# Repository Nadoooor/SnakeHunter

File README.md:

# SnakeHunter
A Handheld device that clones differenet signals like IR, RFID, and more. It has a battery to make it handheld and work without powersource like the laptop.<br>
I made this project because I love cybersecurity specialy networks and the idea of cloneing them. Also, I love hardware so much so combineing the both in one project is sooo cool. 

### Modules used:
- RFID Read/Write
- NRF24L01 Wireless Module With Antenna
- Ublox NEO-6m GPS Module
- Infrared Remote Receiver TSOP JS-1838B
- Infrared LED Diode (Transmitter)
- XL6009 DC-DC Step UP Boost Converter Module (3A) 
### Photos

 <br>

### BOM (Bill Of Materials)
| Item                                                         | Link                                                                                                                                                                                                                                                                                                                                                                                                                                                                                                     | Price                  |
|--------------------------------------------------------------|----------------------------------------------------------------------------------------------------------------------------------------------------------------------------------------------------------------------------------------------------------------------------------------------------------------------------------------------------------------------------------------------------------------------------------------------------------------------------------------------------------|------------------------|
| ESP32 38pins                                                 | [Link](https://mostelectronic.com/shop/arduino-development-boards/esp32-s-38pin-development-board-wifi-and-bluetooth/)                                                                                                                                                                                                                                                                                                                                                                                           | $8.08                  |
| TFT LCD touch screen                                         | [Link](https://www.amazon.com/WWZMDiB-Display-Interface-Arduino-320x240/dp/B0CCHXX1Z9/ref=sr_1_1_sspa?dib=eyJ2IjoiMSJ9.9xYzrIvxxHsHdfW-gksWb3jXxskzgUuA5Zv92-vbF_rgpDSizUJq9ZgjkUXXAnXTFF-g7tu8c3U8-EMJlw-Q9uDaEn5B7V5boVKGWRNHZUFaeOUc-jy6nT_AmLIXFEHbz0vlXF-KDvlwjrPltPtbK0t41pq8tB6F4K7ICLWzThnjkHNXrFFSCCIgBb_lXGixU3_zdR4z01ZQVJP6Scx8_LsG3fd-tv3Qi1mEAhEKbvs.DzTPSmzNNeTbDCBnk1YsSWki1K8MFNSX6Lj1MkVzSLU&dib_tag=se&keywords=tft+display&qid=1752311294&sr=8-1-spons&sp_csd=d2lkZ2V0TmFtZT1zcF9hdGY&psc=1) | $35.07 (with shipping) |
| 3D printed case                                              |                                                                                                                                                                                                                                                                                                                                                                                                                                                                                                          | $10.10                 |
| RFID Read/Write                                              | [Link](https://mostelectronic.com/shop/sensors/rfid-read-write-module-mfrc-522-13-56-mhz/ )                                                                                                                                                                                                                                                                                                                                                                                                                      | $2.42                  |
| Battery X3                                                   | [Link](https://mostelectronic.com/shop/batteries-accessories/rechargeable-batteries/rechargeable-402030-lipo-battery-cell-3-7v-350mah-wire-solder/)                                                                                                                                                                                                                                                                                                                                                          | $3.94                  |
| PCB FR2 Circuit Board (7 x10) cm Pointing                    | [Link](https://mostelectronic.com/shop/pcb/pcb-pcb/pcb-fr2-circuit-board-7-x10-cm-pointing/)                                                                                                                                                                                                                                                                                                                                                                                                                     | $1                     |
| Solder Wire                                                  | [Link](https://mostelectronic.com/shop/tools/soldering-desoldering/solder-wire-singapore-250g-0-6mm-70-30-singapore/)                                                                                                                                                                                                                                                                                                                                                                                            | $11.11                 |
| NRF24L01 Wireless Module With Antenna                        | [Link](https://mostelectronic.com/shop/sensors/nrf24l01-wireless-module-with-antenna/)                                                                                                                                                                                                                                                                                                                                                                                                                           | $6.26                  |
| Cutter Knife                                                 | [Link](https://mostelectronic.com/shop/tools/wire-strippers-nipples-pliers/cutter-knife/)                                                                                                                                                                                                                                                                                                                                                                                                                       | $0.5                   |
| BMS 1S TP4056 (5V -1A) ( Type C ) With Protection            | [Link](https://mostelectronic.com/shop/batteries-accessories/battery-accessories/bms-1s-tp4056-5v-1a-lithium-battery-charger-board-type-c-with-protection/)                                                                                                                                                                                                                                                                                                                                                      | $0.5                   |
| Ublox NEO-6m GPS Module                                      | [Link](https://mostelectronic.com/shop/sensors/ublox-neo-6m-gps-module/)                                                                                                                                                                                                                                                                                                                                                                                                                                        | $9.09                  |
| Infrared Remote Receiver TSOP JS-1838B                       | [Link](https://mostelectronic.com/shop/sensors/infrared-receiver-diode-tl1838-vs1838b/)                                                                                                                                                                                                                                                                                                                                                                                                                         | $0.20                  |
| Infrared LED Diode (Transmitter)                             | [Link](https://mostelectronic.com/shop/sensors/infrared-led-diode-transmitter/)                                                                                                                                                                                                                                                                                                                                                                                                                                  | $0.051                 |
| Micro SD Card Modul                                          | [Link](https://mostelectronic.com/shop/sensors/micro-sd-card-module/)                                                                                                                                                                                                                                                                                                                                                                                                                                            | $1                     |
| XL6009 DC-DC Step UP Boost Converter Module (3A)             | [Link](https://mostelectronic.com/shop/dc-ac-converters/dc-dc-step-up-boost-converter-module-xl6009-3a/)                                                                                                                                                                                                                                                                                                                                                                                                         | $1.41                  |
| DIP Switch 2 Way                                             | [Link](https://mostelectronic.com/shop/components/switches/dip-switch-2-way/)                                                                                                                                                                                                                                                                                                                                                                                                                                    | $0.081                 |
| Connecting Jumper Wires for Breadboard ( 140 Wire – U shape) | [Link](https://mostelectronic.com/shop/wires-crocodiles/u-shape-shield-breadboard-jumper-wires-140pcs/)                                                                                                                                                                                                                                                                                                                                                                                                         | $1.11                  |
|SD card | [Link](https://www.noon.com/egypt-en/canvasselect-plus-micro-sdhc-memory-card-with-adapter-32-gb/N43383398A/p/?o=dd29d760fc2d52bb&shareId=a9b190a7-fcdf-448a-a7b9-24fdeadd19a3) | $5|
| Shipping                                                     |                                                                                                                                                                                                                                                                                                                                                                                                                                                                                                          | $3                     |
| Total                                                        |                                                                                                                                                                                                                                                                                                                                                                                                                                                                                                          | 95$                    |

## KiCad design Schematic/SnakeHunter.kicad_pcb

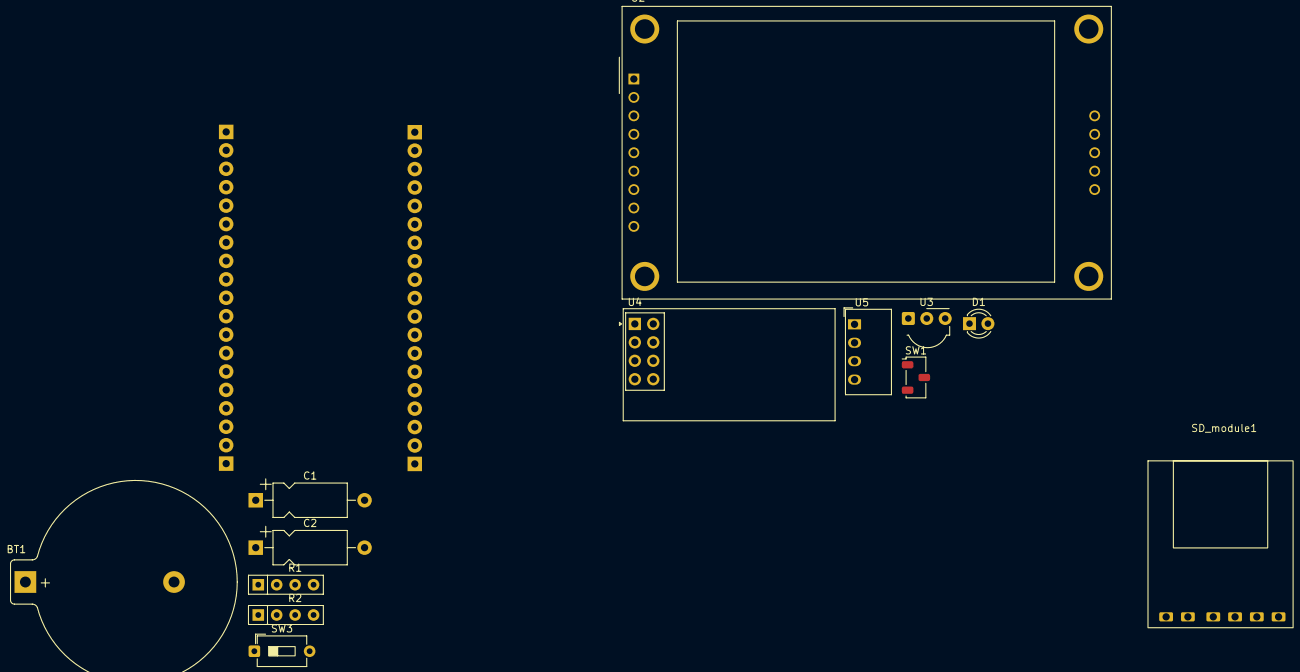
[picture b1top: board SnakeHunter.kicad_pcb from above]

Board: 2 copper layers, 14 parts (0 on the bottom side), 19 nets, no tracks yet.

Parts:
BT1: Battery; BatteryHolder_Keystone_106_1x20mm
C1: C; CP_Axial_L10.0mm_D4.5mm_P15.00mm_Horizontal
C2: C_Polarized; CP_Axial_L10.0mm_D4.5mm_P15.00mm_Horizontal
D1: IR204A; LED_D3.0mm_IRBlack
R1, R2: R; R_Array_SIP4
SD_module1: SD module
SW1: SW_Nidec_CAS-120A1; Nidec_Copal_CAS-120A
SW3: SW_DIP_x02; SW_DIP_SPSTx01_Slide_6.7x4.1mm_W7.62mm_P2.54mm_LowProfile
U1: ESP32-38pin
U2: CR2013-MI2120
U3: TSDP341xx; Vishay_MOLD-3Pin
U4: NRF24L01_Breakout; nRF24L01_Breakout
U5: CRE1S0305S3C; Converter_DCDC_Murata_CRE1xxxxxx3C_THT

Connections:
3v3: C1.1, C2.1, R1.1, R2.1, U1.1 (3.3v), U2.1 (VCC), U3.3 (Vs), U4.2 (VCC)
GND: C1.2, C2.2, D1.1 (K), U1.32 (GND), U1.38 (GND), U3.2 (GND)
unnamed: D1.2 (A), SW3.2
unnamed: R2.2, U1.11 (GPIO27), U4.4 (~CSN)
unnamed: U1.36 (GPIO22), U4.3 (CE)
unnamed: U1.31 (GPIO19), U4.7 (MISO)
unnamed: U1.37 (GPIO23), U4.6 (MOSI)
unnamed: U1.30 (GPIO18), U4.5 (SCK)
unnamed: SW1.3 (A), U5.3 (-VOUT)
unnamed: SW1.2 (B), U1.14 (GND)
unnamed: U1.19 (5V), U5.4 (+VOUT)
unnamed: U1.2 (EN), U2.4 (RESET)
unnamed: U1.24 (GPIO2), U2.5 (D/~C)
unnamed: U1.13 (GPIO12), U2.9 (MISO)
unnamed: U1.15 (GPIO13), U2.6 (MOSI)
unnamed: U1.12 (GPIO14), U2.7 (SCK)
unnamed: U1.23 (GPIO15), U2.3 (~CS)
unnamed: U1.33 (GPIO21), U2.8 (LED)
unnamed: R1.2, SW3.1, U3.1 (OUT)

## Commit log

2025-07-06 Addd
2025-07-06 Remove unused PCB because of using handwiring.
2025-07-12 Rename bottom.step to Production/Case/bottom.step
2025-07-12 Rename Top.step to Production/Case/ Top.step
2025-07-26 Rename Bruce-CYD-2USB.bin to Firmware/Bruce-CYD-2USB.bin
2025-08-06 Schematic moreee cleannn
